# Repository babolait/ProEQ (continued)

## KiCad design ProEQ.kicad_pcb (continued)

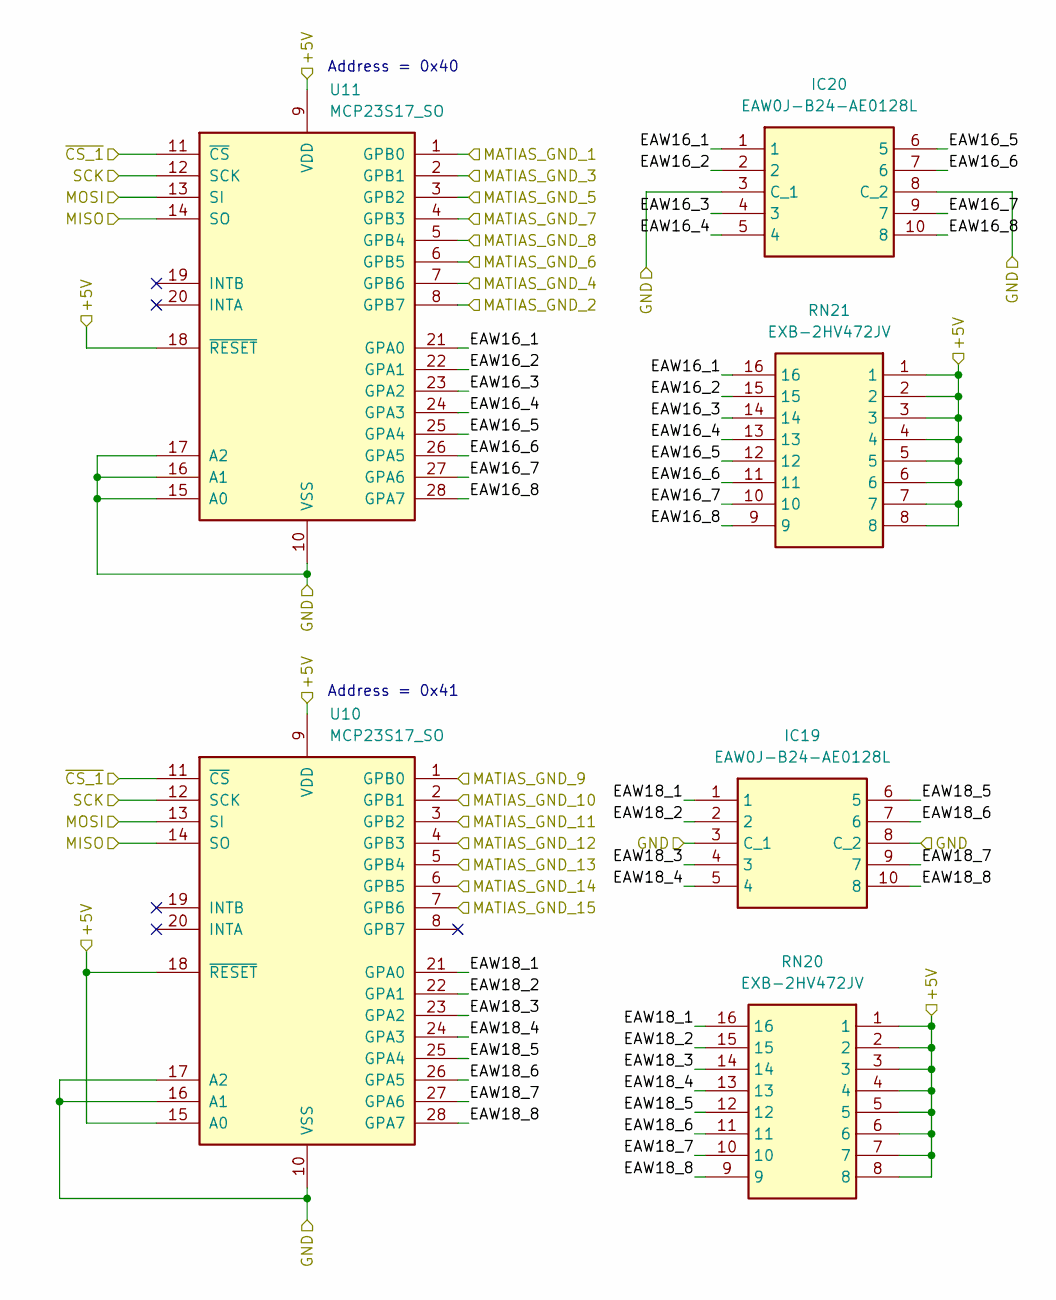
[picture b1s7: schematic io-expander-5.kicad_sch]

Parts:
IC19, IC20: EAW0J-B24-AE0128L; Manufacturer_Part_Number EAW0J-B24-AE0128L; Mouser Part Number 652-EAW0J-B24-AEL
RN20, RN21: EXB-2HV472JV; EXB2HV472JV; Manufacturer_Part_Number EXB-2HV472JV; Mouser Part Number 667-EXB-2HV472JV
U10, U11: MCP23S17_SO; SSOP-28_5.3x10.2mm_P0.65mm; Digikey REF MCP23S17-E/SS-ND

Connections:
+5V: RN20.1, RN20.2, RN20.3, RN20.4, RN20.5, RN20.6, RN20.7, RN20.8, RN21.1, RN21.2, RN21.3, RN21.4, RN21.5, RN21.6, RN21.7, RN21.8, U10.9 (VDD), U10.15 (A0), U10.18 (~RESET), U11.9 (VDD), U11.18 (~RESET); also elsewhere on the board
/IS31FL3743A1_2/MISO: U10.14 (SO), U11.14 (SO); also elsewhere on the board
/IS31FL3743A1_2/MOSI: U10.13 (SI), U11.13 (SI); also elsewhere on the board
/IS31FL3743A1_2/SCK: U10.12 (SCK), U11.12 (SCK); also elsewhere on the board
/MCP23017 + EAW_4/EAW16_1: IC20.1, RN21.16, U11.21 (GPA0)
/MCP23017 + EAW_4/EAW16_2: IC20.2, RN21.15, U11.22 (GPA1)
/MCP23017 + EAW_4/EAW16_3: IC20.4 (3), RN21.14, U11.23 (GPA2)
/MCP23017 + EAW_4/EAW16_4: IC20.5 (4), RN21.13, U11.24 (GPA3)
/MCP23017 + EAW_4/EAW16_5: IC20.6 (5), RN21.12, U11.25 (GPA4)
/MCP23017 + EAW_4/EAW16_6: IC20.7 (6), RN21.11, U11.26 (GPA5)
/MCP23017 + EAW_4/EAW16_7: IC20.9 (7), RN21.10, U11.27 (GPA6)
/MCP23017 + EAW_4/EAW16_8: IC20.10 (8), RN21.9, U11.28 (GPA7)
/MCP23017 + EAW_4/EAW18_1: IC19.1, RN20.16, U10.21 (GPA0)
/MCP23017 + EAW_4/EAW18_2: IC19.2, RN20.15, U10.22 (GPA1)
/MCP23017 + EAW_4/EAW18_3: IC19.4 (3), RN20.14, U10.23 (GPA2)
/MCP23017 + EAW_4/EAW18_4: IC19.5 (4), RN20.13, U10.24 (GPA3)
/MCP23017 + EAW_4/EAW18_5: IC19.6 (5), RN20.12, U10.25 (GPA4)
/MCP23017 + EAW_4/EAW18_6: IC19.7 (6), RN20.11, U10.26 (GPA5)
/MCP23017 + EAW_4/EAW18_7: IC19.9 (7), RN20.10, U10.27 (GPA6)
/MCP23017 + EAW_4/EAW18_8: IC19.10 (8), RN20.9, U10.28 (GPA7)
/MCP23017 + EAW_4/MATIAS_GND_1: U11.1 (GPB0); also elsewhere on the board
/MCP23017 + EAW_4/MATIAS_GND_2: U11.8 (GPB7); also elsewhere on the board
/MCP23017 + EAW_4/MATIAS_GND_3: U11.2 (GPB1); also elsewhere on the board
/MCP23017 + EAW_4/MATIAS_GND_4: U11.7 (GPB6); also elsewhere on the board
/MCP23017 + EAW_4/MATIAS_GND_5: U11.3 (GPB2); also elsewhere on the board
/MCP23017 + EAW_4/MATIAS_GND_6: U11.6 (GPB5); also elsewhere on the board
/MCP23017 + EAW_4/MATIAS_GND_7: U11.4 (GPB3); also elsewhere on the board
/MCP23017 + EAW_4/MATIAS_GND_8: U11.5 (GPB4); also elsewhere on the board
/MCP23017 + EAW_4/MATIAS_GND_9: U10.1 (GPB0); also elsewhere on the board
/MCP23017 + EAW_4/MATIAS_GND_10: U10.2 (GPB1); also elsewhere on the board
/MCP23017 + EAW_4/MATIAS_GND_11: U10.3 (GPB2); also elsewhere on the board
/MCP23017 + EAW_4/MATIAS_GND_12: U10.4 (GPB3); also elsewhere on the board
/MCP23017 + EAW_4/MATIAS_GND_13: U10.5 (GPB4); also elsewhere on the board
/MCP23017 + EAW_4/MATIAS_GND_14: U10.6 (GPB5); also elsewhere on the board
/MCP23017 + EAW_4/MATIAS_GND_15: U10.7 (GPB6); also elsewhere on the board
/MCP23017 + EAW_4/~CS_1: U10.11 (~CS), U11.11 (~CS); also elsewhere on the board
GND: IC19.3 (C_1), IC19.8 (C_2), IC20.3 (C_1), IC20.8 (C_2), U10.10 (VSS), U10.16 (A1), U10.17 (A2), U11.10 (VSS), U11.15 (A0), U11.16 (A1), U11.17 (A2); also elsewhere on the board

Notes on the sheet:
Address = 0x41
Address = 0x40

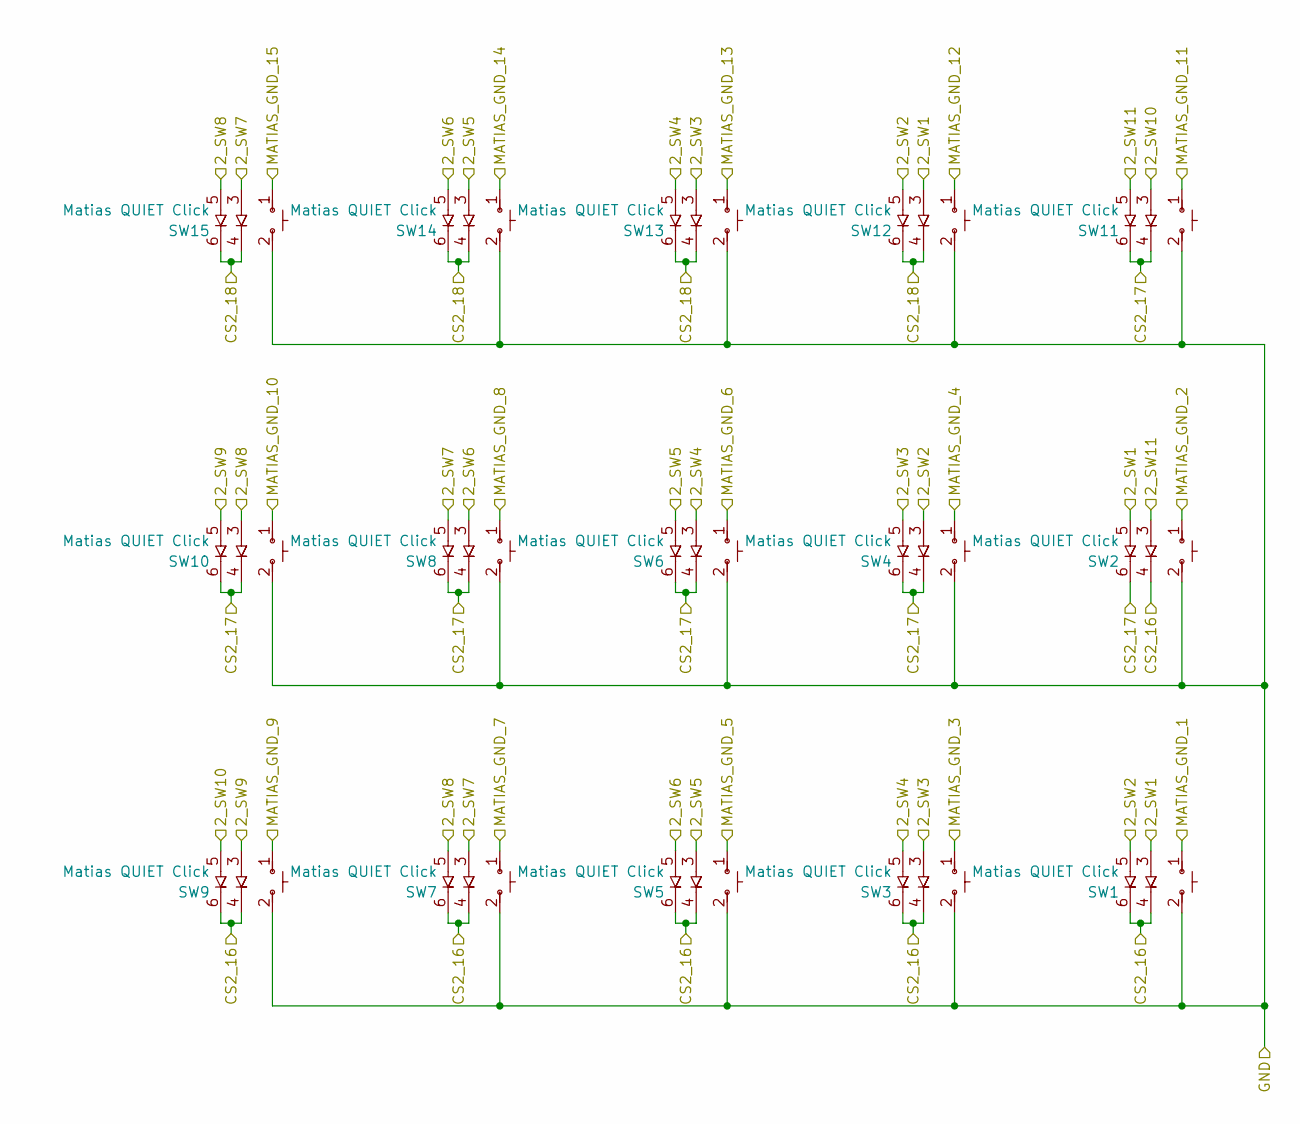
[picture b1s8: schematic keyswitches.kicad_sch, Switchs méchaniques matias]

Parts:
SW1, SW2, SW3, SW4, SW5, SW6, SW7, SW8, SW9, SW10, SW11, SW12, SW13, SW14, SW15: Matias QUIET Click; SW_Matias_QC_2LED

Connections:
/IS31FL3743A1_2/2_SW1: SW1.3, SW2.5, SW12.3; also elsewhere on the board
/IS31FL3743A1_2/2_SW2: SW1.5, SW4.3, SW12.5; also elsewhere on the board
/IS31FL3743A1_2/2_SW3: SW3.3, SW4.5, SW13.3; also elsewhere on the board
/IS31FL3743A1_2/2_SW4: SW3.5, SW6.3, SW13.5; also elsewhere on the board
/IS31FL3743A1_2/2_SW5: SW5.3, SW6.5, SW14.3; also elsewhere on the board
/IS31FL3743A1_2/2_SW6: SW5.5, SW8.3, SW14.5; also elsewhere on the board
/IS31FL3743A1_2/2_SW7: SW7.3, SW8.5, SW15.3; also elsewhere on the board
/IS31FL3743A1_2/2_SW8: SW7.5, SW10.3, SW15.5; also elsewhere on the board
/IS31FL3743A1_2/2_SW9: SW9.3, SW10.5; also elsewhere on the board
/IS31FL3743A1_2/2_SW10: SW9.5, SW11.3; also elsewhere on the board
/IS31FL3743A1_2/2_SW11: SW2.3, SW11.5; also elsewhere on the board
/IS31FL3743A1_2/CS2_16: SW1.4, SW1.6, SW2.4, SW3.4, SW3.6, SW5.4, SW5.6, SW7.4, SW7.6, SW9.4, SW9.6; also elsewhere on the board
/IS31FL3743A1_2/CS2_17: SW2.6, SW4.4, SW4.6, SW6.4, SW6.6, SW8.4, SW8.6, SW10.4, SW10.6, SW11.4, SW11.6; also elsewhere on the board
/IS31FL3743A1_2/CS2_18: SW12.4, SW12.6, SW13.4, SW13.6, SW14.4, SW14.6, SW15.4, SW15.6; also elsewhere on the board
/MCP23017 + EAW_4/MATIAS_GND_1: SW1.1; also elsewhere on the board
/MCP23017 + EAW_4/MATIAS_GND_2: SW2.1; also elsewhere on the board
/MCP23017 + EAW_4/MATIAS_GND_3: SW3.1; also elsewhere on the board
/MCP23017 + EAW_4/MATIAS_GND_4: SW4.1; also elsewhere on the board
/MCP23017 + EAW_4/MATIAS_GND_5: SW5.1; also elsewhere on the board
/MCP23017 + EAW_4/MATIAS_GND_6: SW6.1; also elsewhere on the board
/MCP23017 + EAW_4/MATIAS_GND_7: SW7.1; also elsewhere on the board
/MCP23017 + EAW_4/MATIAS_GND_8: SW8.1; also elsewhere on the board
/MCP23017 + EAW_4/MATIAS_GND_9: SW9.1; also elsewhere on the board
/MCP23017 + EAW_4/MATIAS_GND_10: SW10.1; also elsewhere on the board
/MCP23017 + EAW_4/MATIAS_GND_11: SW11.1; also elsewhere on the board
/MCP23017 + EAW_4/MATIAS_GND_12: SW12.1; also elsewhere on the board
/MCP23017 + EAW_4/MATIAS_GND_13: SW13.1; also elsewhere on the board
/MCP23017 + EAW_4/MATIAS_GND_14: SW14.1; also elsewhere on the board
/MCP23017 + EAW_4/MATIAS_GND_15: SW15.1; also elsewhere on the board
GND: SW1.2, SW2.2, SW3.2, SW4.2, SW5.2, SW6.2, SW7.2, SW8.2, SW9.2, SW10.2, SW11.2, SW12.2, SW13.2, SW14.2, SW15.2; also elsewhere on the board

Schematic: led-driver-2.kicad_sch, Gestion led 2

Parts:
C12, C14: 1uF; C_0603_1608Metric_Pad1.08x0.95mm_HandSolder; LCSC C15849
C13, C15, C16: 100nF; C_0603_1608Metric_Pad1.08x0.95mm_HandSolder; LCSC C14663
D201, D202, D203, D204, D212, D213, D214, D215, D223, D224, D225, D226, D234, D235, D236, D237, D245, D246, D247, D248, D256, D257, D258, D259, D267, D268, D269, D270, D278, D279, D280, D281, D289, D290, D291, D292, D300, D301, D302, D303, D311, D312, D313, D314, D322, D323, D324, D325, D333, D334, D335, D336, D344, D345, D346, D347, D355, D356, D357, D358, D366, D367, D368, D369, D377, D378, D379, D380, D388, D389, D390, D391: LED_inv; SMLZ24E2N3TT86_VLP; LCSC C20110232
R11: 10k; R_0603_1608Metric_Pad0.98x0.95mm_HandSolder; LCSC C25804
R12: 100k; R_0603_1608Metric_Pad0.98x0.95mm_HandSolder; LCSC C25803
R13, R14: 20; R_0603_1608Metric_Pad0.98x0.95mm_HandSolder; Digikey REF P20.00BYCT-ND
RN1, RN23: YC248-JR-0720RL; EXB2HV472JV; Manufacturer_Part_Number EXB-2HV472JV; Mouser Part Number 667-EXB-2HV472JV
U14: IS31FL3743B-QULS4-TR; IS31FL3743A; LCSC C2962218

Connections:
2_CS9: RN23.1, U14.31 (CS9)
2_CS10: RN23.2, U14.21 (CS10)
+5V: C12.1, C13.1, C14.1, C15.1, U14.5 (P_{VCC}), U14.22 (VCC); also elsewhere on the board
/IS31FL3743A1_2/2_SW1: D201.1 (A), D212.1 (A), D223.1 (A), D234.1 (A), D245.1 (A), D256.1 (A), D267.1 (A), D278.1 (A), D289.1 (A), D300.1 (A), D311.1 (A), D322.1 (A), D333.1 (A), D344.1 (A), D355.1 (A), D366.1 (A), D377.1 (A), D388.1 (A), U14.6 (SW1); also elsewhere on the board
/IS31FL3743A1_2/2_SW2: D202.1 (A), D213.1 (A), D224.1 (A), D235.1 (A), D246.1 (A), D257.1 (A), D268.1 (A), D279.1 (A), D290.1 (A), D301.1 (A), D312.1 (A), D323.1 (A), D334.1 (A), D345.1 (A), D356.1 (A), D367.1 (A), D378.1 (A), D389.1 (A), U14.4 (SW2); also elsewhere on the board
/IS31FL3743A1_2/2_SW3: D203.1 (A), D214.1 (A), D225.1 (A), D236.1 (A), D247.1 (A), D258.1 (A), D269.1 (A), D280.1 (A), D291.1 (A), D302.1 (A), D313.1 (A), D324.1 (A), D335.1 (A), D346.1 (A), D357.1 (A), D368.1 (A), D379.1 (A), D390.1 (A), U14.7 (SW3); also elsewhere on the board
/IS31FL3743A1_2/2_SW4: D204.1 (A), D215.1 (A), D226.1 (A), D237.1 (A), D248.1 (A), D259.1 (A), D270.1 (A), D281.1 (A), D292.1 (A), D303.1 (A), D314.1 (A), D325.1 (A), D336.1 (A), D347.1 (A), D358.1 (A), D369.1 (A), D380.1 (A), D391.1 (A), U14.3 (SW4); also elsewhere on the board
/IS31FL3743A1_2/2_SW5: U14.8 (SW5); also elsewhere on the board
/IS31FL3743A1_2/2_SW6: U14.2 (SW6); also elsewhere on the board
/IS31FL3743A1_2/2_SW7: U14.9 (SW7); also elsewhere on the board
/IS31FL3743A1_2/2_SW8: U14.1 (SW8); also elsewhere on the board
/IS31FL3743A1_2/2_SW9: U14.10 (SW9); also elsewhere on the board
/IS31FL3743A1_2/2_SW10: U14.40 (SW10); also elsewhere on the board
/IS31FL3743A1_2/2_SW11: U14.11 (SW11); also elsewhere on the board
/IS31FL3743A1_2/+3.3V: C16.1, R12.1, U14.26 (SDB); also elsewhere on the board
/IS31FL3743A1_2/CS2_16: D223.2 (K), D224.2 (K), D225.2 (K), D226.2 (K), RN23.9; also elsewhere on the board
/IS31FL3743A1_2/CS2_17: D212.2 (K), D213.2 (K), D214.2 (K), D215.2 (K), R14.2; also elsewhere on the board
/IS31FL3743A1_2/CS2_18: D201.2 (K), D202.2 (K), D203.2 (K), D204.2 (K), R13.2; also elsewhere on the board
/IS31FL3743A1_2/MISO: U14.24 (MISO); also elsewhere on the board
/IS31FL3743A1_2/MOSI: U14.28 (MOSI); also elsewhere on the board
/IS31FL3743A1_2/SCK: U14.27 (SCK); also elsewhere on the board
/IS31FL3743A1_2/~CS_2: U14.25 (~CS); also elsewhere on the board
CS2_1: D388.2 (K), D389.2 (K), D390.2 (K), D391.2 (K), RN1.8
CS2_2: D377.2 (K), D378.2 (K), D379.2 (K), D380.2 (K), RN1.7
CS2_3: D366.2 (K), D367.2 (K), D368.2 (K), D369.2 (K), RN1.6
CS2_4: D355.2 (K), D356.2 (K), D357.2 (K), D358.2 (K), RN1.5
CS2_5: D344.2 (K), D345.2 (K), D346.2 (K), D347.2 (K), RN1.4
CS2_6: D333.2 (K), D334.2 (K), D335.2 (K), D336.2 (K), RN1.3
CS2_7: D322.2 (K), D323.2 (K), D324.2 (K), D325.2 (K), RN1.2
CS2_8: D311.2 (K), D312.2 (K), D313.2 (K), D314.2 (K), RN1.1
CS2_9: D300.2 (K), D301.2 (K), D302.2 (K), D303.2 (K), RN23.16
CS2_10: D289.2 (K), D290.2 (K), D291.2 (K), D292.2 (K), RN23.15
CS2_11: D278.2 (K), D279.2 (K), D280.2 (K), D281.2 (K), RN23.14
CS2_12: D267.2 (K), D268.2 (K), D269.2 (K), D270.2 (K), RN23.13
CS2_13: D256.2 (K), D257.2 (K), D258.2 (K), D259.2 (K), RN23.12
CS2_14: D245.2 (K), D246.2 (K), D247.2 (K), D248.2 (K), RN23.11
CS2_15: D234.2 (K), D235.2 (K), D236.2 (K), D237.2 (K), RN23.10
GND: C12.2, C13.2, C14.2, C15.2, C16.2, R11.2, R12.2, U14.16 (P_{GND}), U14.23 (GND), U14.41 (P_{GND}); also elsewhere on the board
unnamed: RN1.9, U14.39 (CS1)
unnamed: RN1.10, U14.38 (CS2)
unnamed: RN1.11, U14.37 (CS3)
unnamed: RN1.12, U14.36 (CS4)
unnamed: RN1.13, U14.35 (CS5)
unnamed: RN1.14, U14.34 (CS6)
unnamed: RN1.15, U14.33 (CS7)
unnamed: RN1.16, U14.32 (CS8)
unnamed: RN23.3, U14.20 (CS11)
unnamed: RN23.4, U14.19 (CS12)
unnamed: RN23.5, U14.18 (CS13)
unnamed: RN23.6, U14.17 (CS14)
unnamed: RN23.7, U14.15 (CS15)
unnamed: RN23.8, U14.14 (CS16)
unnamed: R14.1, U14.13 (CS17)
unnamed: R13.1, U14.12 (CS18)
unnamed: R11.1, U14.29 (I_{set})

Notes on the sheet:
address = 0bX101000X
The 20R and 50R between LED and IC is only for thermal reduction, for mono red LED, if PV CC =V CC =3.3V, don't need these resistors
OUTs for SW LEDS

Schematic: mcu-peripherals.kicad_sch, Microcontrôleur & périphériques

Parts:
A1: Arduino_UNO_R3
J2: Conn_01x07; PinHeader_1x07_P2.54mm_Vertical
J4, J6: Conn_01x11; PinHeader_1x11_P2.54mm_Vertical
J5, J16: Conn_01x01; PinHeader_1x01_P2.54mm_Vertical
R4, R5: 4k7; R_0603_1608Metric_Pad0.98x0.95mm_HandSolder; Digikey REF RMCF0603FT4K70CT-ND
R15, R16, R17, R18, R19, R20, R21, R22, R23, R24, R25, R26, R27, R28, R29, R30, R31, R32, R33, R34: 10k; R_0603_1608Metric_Pad0.98x0.95mm_HandSolder; Digikey REF RMCF0603JT10K0CT-ND
TP1, TP2, TP5, TP6, TP7, TP8, TP9, TP11, TP12, TP13: TestPoint; PinHeader_1x01_P2.54mm_Vertical

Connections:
+5V: J4.1, J6.1, R4.1, R5.1, R16.1, R25.1; also elsewhere on the board
/Alimentation/+5V USB: A1.5 (+5V); also elsewhere on the board
/IS31FL3743A1_2/+3.3V: A1.4 (3V3); also elsewhere on the board
/IS31FL3743A1_2/MISO: A1.27 (D12), TP8.1; also elsewhere on the board
/IS31FL3743A1_2/MOSI: A1.26 (D11), TP7.1; also elsewhere on the board
/IS31FL3743A1_2/SCK: A1.28 (D13), TP9.1; also elsewhere on the board
/IS31FL3743A1_2/~CS_2: A1.12 (A3), TP13.1; also elsewhere on the board
/MCP23017 + EAW/~CS_0: A1.17 (D2), TP11.1; also elsewhere on the board
/MCP23017 + EAW_4/~CS_1: A1.18 (D3), TP12.1; also elsewhere on the board
GND: A1.6 (GND), A1.7 (GND), A1.29 (GND), J4.11, J6.11, R24.2, R34.2; also elsewhere on the board
unnamed: A1.9 (A0), J5.1
unnamed: A1.10 (A1), J16.1
unnamed: A1.15 (D0/RX), TP1.1
unnamed: A1.16 (D1/TX), TP2.1
unnamed: A1.19 (D4), J2.1
unnamed: A1.20 (D5), J2.2
unnamed: A1.21 (D6), J2.3
unnamed: A1.22 (D7), J2.4
unnamed: A1.23 (D8), J2.5
unnamed: A1.24 (D9), J2.6
unnamed: A1.25 (D10), J2.7
unnamed: A1.14 (SCL/A5), R5.2, TP6.1
unnamed: A1.13 (SDA/A4), R4.2, TP5.1
unnamed: J4.2, R15.1, R16.2
unnamed: J4.3, R15.2, R17.1
unnamed: J4.4, R17.2, R18.1
unnamed: J4.5, R18.2, R19.1
unnamed: J4.6, R19.2, R20.1
unnamed: J4.7, R20.2, R21.1
unnamed: J4.8, R21.2, R22.1
unnamed: J4.9, R22.2, R23.1
unnamed: J4.10, R23.2, R24.1
unnamed: J6.2, R25.2, R26.1
unnamed: J6.3, R26.2, R27.1
unnamed: J6.4, R27.2, R28.1
unnamed: J6.5, R28.2, R29.1
unnamed: J6.6, R29.2, R30.1
unnamed: J6.7, R30.2, R31.1
unnamed: J6.8, R31.2, R32.1
unnamed: J6.9, R32.2, R33.1
unnamed: J6.10, R33.2, R34.1

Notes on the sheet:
Resistor ladder

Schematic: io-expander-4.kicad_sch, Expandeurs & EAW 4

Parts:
IC14, IC15, IC16, IC17: EAW0J-B24-AE0128L; Manufacturer_Part_Number EAW0J-B24-AE0128L; Mouser Part Number 652-EAW0J-B24-AEL
RN15, RN16, RN17, RN18: EXB-2HV472JV; EXB2HV472JV; Manufacturer_Part_Number EXB-2HV472JV; Mouser Part Number 667-EXB-2HV472JV
U8, U9: MCP23S17_SO; SSOP-28_5.3x10.2mm_P0.65mm; Digikey REF MCP23S17-E/SS-ND

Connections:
+5V: RN15.1, RN15.2, RN15.3, RN15.4, RN15.5, RN15.6, RN15.7, RN15.8, RN16.1, RN16.2, RN16.3, RN16.4, RN16.5, RN16.6, RN16.7, RN16.8, RN17.1, RN17.2, RN17.3, RN17.4, RN17.5, RN17.6, RN17.7, RN17.8, RN18.1, RN18.2, RN18.3, RN18.4, RN18.5, RN18.6, RN18.7, RN18.8, U8.9 (VDD), U8.16 (A1), U8.17 (A2), U8.18 (~RESET), U9.9 (VDD), U9.15 (A0), U9.16 (A1), U9.17 (A2), U9.18 (~RESET); also elsewhere on the board
/IS31FL3743A1_2/MISO: U8.14 (SO), U9.14 (SO); also elsewhere on the board
/IS31FL3743A1_2/MOSI: U8.13 (SI), U9.13 (SI); also elsewhere on the board
/IS31FL3743A1_2/SCK: U8.12 (SCK), U9.12 (SCK); also elsewhere on the board
/MCP23017 + EAW/~CS_0: U8.11 (~CS), U9.11 (~CS); also elsewhere on the board
/MCP23017 + EAW_3/EAW12_1: IC16.1, RN17.16, U8.21 (GPA0)
/MCP23017 + EAW_3/EAW12_2: IC16.2, RN17.15, U8.22 (GPA1)
/MCP23017 + EAW_3/EAW12_3: IC16.4 (3), RN17.14, U8.23 (GPA2)
/MCP23017 + EAW_3/EAW12_4: IC16.5 (4), RN17.13, U8.24 (GPA3)
/MCP23017 + EAW_3/EAW12_5: IC16.6 (5), RN17.12, U8.25 (GPA4)
/MCP23017 + EAW_3/EAW12_6: IC16.7 (6), RN17.11, U8.26 (GPA5)
/MCP23017 + EAW_3/EAW12_7: IC16.9 (7), RN17.10, U8.27 (GPA6)
/MCP23017 + EAW_3/EAW12_8: IC16.10 (8), RN17.9, U8.28 (GPA7)
/MCP23017 + EAW_3/EAW13_1: IC14.1, RN15.16, U8.1 (GPB0)
/MCP23017 + EAW_3/EAW13_2: IC14.2, RN15.15, U8.2 (GPB1)
/MCP23017 + EAW_3/EAW13_3: IC14.4 (3), RN15.14, U8.3 (GPB2)
/MCP23017 + EAW_3/EAW13_4: IC14.5 (4), RN15.13, U8.4 (GPB3)
/MCP23017 + EAW_3/EAW13_5: IC14.6 (5), RN15.12, U8.5 (GPB4)
/MCP23017 + EAW_3/EAW13_6: IC14.7 (6), RN15.11, U8.6 (GPB5)
/MCP23017 + EAW_3/EAW13_7: IC14.9 (7), RN15.10, U8.7 (GPB6)
/MCP23017 + EAW_3/EAW13_8: IC14.10 (8), RN15.9, U8.8 (GPB7)
/MCP23017 + EAW_3/EAW14_1: IC17.1, RN18.16, U9.21 (GPA0)
/MCP23017 + EAW_3/EAW14_2: IC17.2, RN18.15, U9.22 (GPA1)
/MCP23017 + EAW_3/EAW14_3: IC17.4 (3), RN18.14, U9.23 (GPA2)
/MCP23017 + EAW_3/EAW14_4: IC17.5 (4), RN18.13, U9.24 (GPA3)
/MCP23017 + EAW_3/EAW14_5: IC17.6 (5), RN18.12, U9.25 (GPA4)
/MCP23017 + EAW_3/EAW14_6: IC17.7 (6), RN18.11, U9.26 (GPA5)
/MCP23017 + EAW_3/EAW14_7: IC17.9 (7), RN18.10, U9.27 (GPA6)
/MCP23017 + EAW_3/EAW14_8: IC17.10 (8), RN18.9, U9.28 (GPA7)
/MCP23017 + EAW_3/EAW15_1: IC15.1, RN16.16, U9.1 (GPB0)
/MCP23017 + EAW_3/EAW15_2: IC15.2, RN16.15, U9.2 (GPB1)
/MCP23017 + EAW_3/EAW15_3: IC15.4 (3), RN16.14, U9.3 (GPB2)
/MCP23017 + EAW_3/EAW15_4: IC15.5 (4), RN16.13, U9.4 (GPB3)
/MCP23017 + EAW_3/EAW15_5: IC15.6 (5), RN16.12, U9.5 (GPB4)
/MCP23017 + EAW_3/EAW15_6: IC15.7 (6), RN16.11, U9.6 (GPB5)
/MCP23017 + EAW_3/EAW15_7: IC15.9 (7), RN16.10, U9.7 (GPB6)
/MCP23017 + EAW_3/EAW15_8: IC15.10 (8), RN16.9, U9.8 (GPB7)
GND: IC14.3 (C_1), IC14.8 (C_2), IC15.3 (C_1), IC15.8 (C_2), IC16.3 (C_1), IC16.8 (C_2), IC17.3 (C_1), IC17.8 (C_2), U8.10 (VSS), U8.15 (A0), U9.10 (VSS); also elsewhere on the board

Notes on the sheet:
Address = 0x47
Address = 0x46

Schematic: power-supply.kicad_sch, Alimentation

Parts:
C1: 100nF; C_0603_1608Metric_Pad1.08x0.95mm_HandSolder; LCSC C14663
C2: 10pF; C_0603_1608Metric_Pad1.08x0.95mm_HandSolder; LCSC C1634
C3, C4: 22uF; C_0805_2012Metric; Digikey REF 22uF,1276-2910-1-ND
C5: 100uF; CP_Radial_D5.0mm_P2.00mm; Digikey REF 1189-25YXS100MEFC5X11-ND
C6: 10uF; C_0603_1608Metric_Pad1.08x0.95mm_HandSolder; Digikey REF 445-C1608X5R1E106M080DCCT-ND
C17, C18: 1uF; C_0805_2012Metric; LCSC C28323
D1: PMEG4030ER; Nexperia_CFP3_SOD-123W; Digikey REF 5272-PMEG4030ERCT-ND
D2: vert; D_0805_2012Metric_Pad1.15x1.40mm_HandSolder; Digikey REF 754-1127-1-ND
J1: Power IN (<9V); PinHeader_1x02_P2.54mm_Vertical
L1: 3,3uH; L_Changjiang_FNR6040S; Digikey REF 732-5545-1-ND
R1: 52,3k; R_0603_1608Metric_Pad0.98x0.95mm_HandSolder; Digikey REF CR0603-FX-5232ELFCT-ND
R2: 1k; R_0603_1608Metric_Pad0.98x0.95mm_HandSolder; Digikey REF 311-1.00KHRCT-ND
R3, R35: 10k; R_0603_1608Metric_Pad0.98x0.95mm_HandSolder; Digikey REF RMCF0603JT10K0CT-ND
TP4, TP10: TestPoint; PinHeader_1x01_P2.54mm_Vertical
U1: AP62301WU; TSOT-23-6_HandSoldering; Digikey REF 31-AP62301WU-7CT-ND
U12: LM66200DRLR; SOT-583-8_HandSolder; LCSC C3235556

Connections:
+5V: TP10.1, U12.2 (V_{out}), U12.7 (V_{out}); also elsewhere on the board
/Alimentation/+5V USB: C18.1, U12.6 (V_{in2}); also elsewhere on the board
/Alimentation/SW FOR COPPER AREA: C1.1, L1.1, U1.2 (SW)
/Alimentation/VIN FOR COPPER: C5.1, C6.1, D1.1 (K), U1.3 (IN)
/Alimentation/Zone Vin 1: C2.1, C3.1, C4.1, C17.1, L1.2, R1.1, R2.1, R35.1, U12.3 (V_{in1})
GND: C3.2, C4.2, C5.2, C6.2, C17.2, C18.2, D2.1 (K), J1.1, R3.2, TP4.1, U1.1 (GND), U12.1 (GND), U12.5 (GND); also elsewhere on the board
unnamed: D1.2 (A), J1.2
unnamed: D2.2 (A), R2.2
unnamed: C1.2, U1.6 (BST)
unnamed: C2.2, R1.2, R3.1, U1.4 (FB)
unnamed: R35.2, U12.8 (ST)

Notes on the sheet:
1.5A peak
Decoupling for LM66 inputs
25mA par MCP23s17 9 x 25 = 225 mA 40mA par matias led 15 x 40 = 600 mA 1mA par led 271 x 1 --> 300 mA 190mA pour VFD 1 x 190 = 190 mA 30 mA pour Arduino 1 x 30 = 30 mA = 1,345 A -->

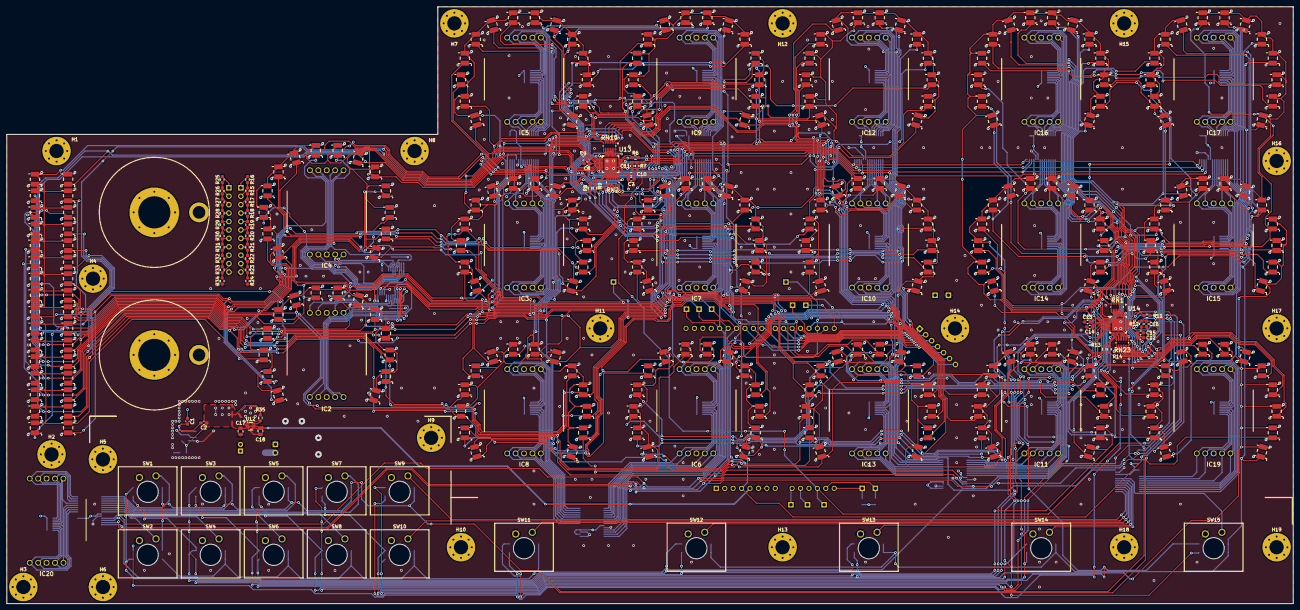
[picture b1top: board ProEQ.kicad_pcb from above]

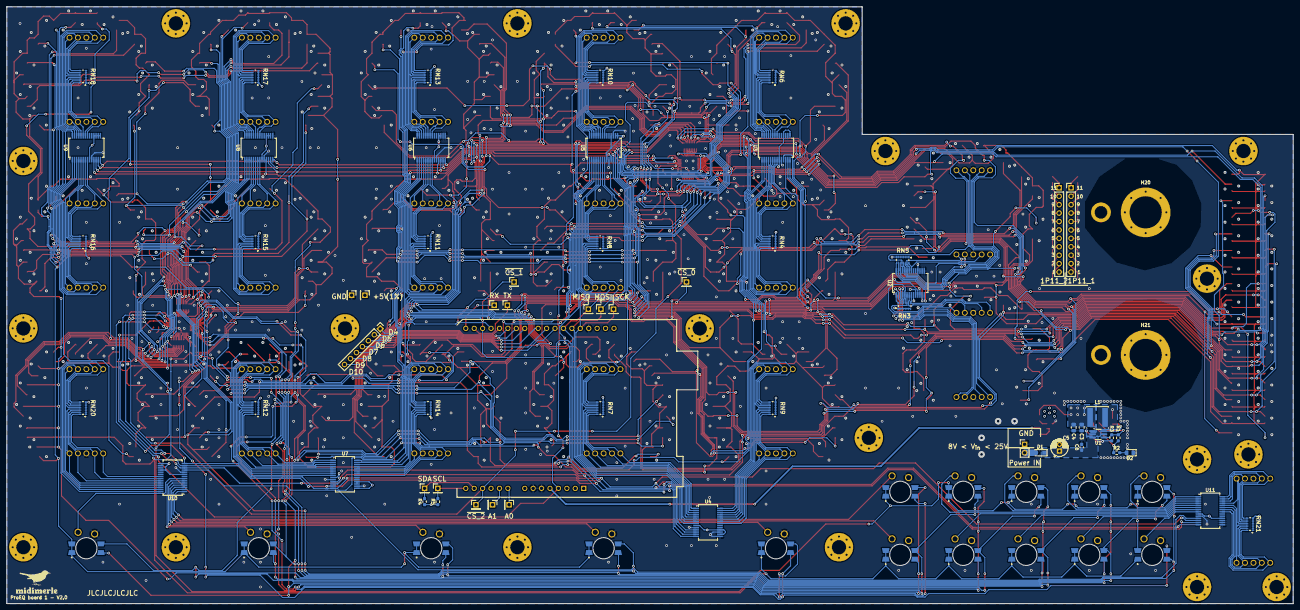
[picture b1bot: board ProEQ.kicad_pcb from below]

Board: 4 copper layers, 388.0 x 180.0 mm, 435 parts (63 on the bottom side), 304 nets.

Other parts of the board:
FID1: Fiducial; midimerle_logo

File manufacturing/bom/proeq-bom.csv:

Id,Designator,Footprint,Quantity,Designation,Supplier and ref
1,"D91,D96,D224,D160,D156,D259,D99,D38,D183,D143,D23,D116,D281,D124,D130,D155,D15,D225,D82,D24,D301,D55,D77,D193,D292,D10,D92,D270,D290,D366,D54,D192,D136,D27,D347,D68,D335,D133,D153,D102,D111,D36,D336,D53,D70,D109,D86,D61,D11,D345,D369,D158,D267,D83,D13,D177,D9,D245,D94,D379,D72,D151,D247,D118,D181,D166,D76,D95,D174,D106,D122,D291,D81,D129,D197,D182,D186,D171,D324,D58,D110,D78,D356,D149,D333,D170,D185,D191,D390,D300,D164,D148,D289,D314,D367,D131,D16,D355,D202,D269,D34,D45,D223,D120,D97,D258,D246,D180,D44,D163,D146,D165,D4,D37,D280,D113,D25,D90,D43,D69,D187,D66,D388,D257,D346,D79,D127,D57,D162,D107,D179,D167,D157,D65,D134,D5,D126,D85,D168,D64,D358,D237,D132,D80,D20,D196,D215,D380,D204,D52,D368,D26,D98,D137,D123,D18,D150,D29,D101,D22,D117,D142,D41,D311,D175,D60,D173,D62,D121,D105,D89,D378,D313,D84,D235,D3,D47,D154,D322,D138,D279,D88,D391,D188,D21,D6,D14,D140,D214,D147,D114,D31,D389,D161,D139,D112,D312,D56,D213,D12,D323,D203,D42,D28,D145,D152,D103,D48,D115,D59,D51,D234,D248,D268,D377,D75,D67,D35,D30,D172,D194,D108,D87,D190,D49,D189,D199,D201,D226,D135,D176,D344,D8,D357,D32,D93,D184,D212,D256,D325,D159,D74,D198,D17,D19,D141,D169,D236,D303,D178,D200,D46,D278,D73,D33,D71,D104,D195,D119,D302,D50,D39,D128,D100,D144,D125,D63,D40,D7,D334",SMLZ24E2N3TT86 + VLP,270,LED_inv,846-SMLZ24E2N3TT86CT-ND
2,"C13,C8,C15,C11,C10,C16",C_0603_1608Metric_Pad1.08x0.95mm_HandSolder,6,"0,1uF",1276-1935-1-ND
3,"IC15,IC5,IC11,IC12,IC6,IC9,IC4,IC19,IC3,IC13,IC8,IC10,IC14,IC2,IC16,IC7,IC17,IC20",EAW0J-B24-AE0128L,18,EAW0J-B24-AE0128L,EAW0J-B24-AE0128L-ND
4,"H14,H19,H1,H12,H8,H18,H11,H2,H17,H6,H3,H16,H5,H9,H7,H10,H4,H13,H15",MountingHole_4.5mm_Pad_Via,19,MountingHole_Pad,
5,"SW8,SW4,SW13,SW11,SW12,SW9,SW6,SW1,SW5,SW2,SW14,SW3,SW15,SW7,SW10",SW_Matias_QC,15,Matias QUIET Click,
6,"RN23,RN19,RN1,RN2",EXB2HV472JV,4,YC248-JR-0720RL,13-YC248-JR-0720RLCT-ND
7,C1,C_1206_3216Metric,1,100nF,1276-1017-1-ND
8,"R13,R9,R8,R14",R_0603_1608Metric_Pad0.98x0.95mm_HandSolder,4,20,P20.00BYCT-ND
9,"C9,C14,C7,C12",C_0603_1608Metric_Pad1.08x0.95mm_HandSolder,4,1uF,1276-1102-1-ND
10,"R7,R12,A13,A2,A7,A23,R10,A16,A4,A15,A14,A19,A9,A12,A10,A18,A21,A22,A24,A26,A8,A17,A11,A27,A30,A5,A25,A6,A29,A20,A3,A31",R_0603_1608Metric_Pad0.98x0.95mm_HandSolder,32,100k,311-100KHRCT-ND
11,C2,C_1206_3216Metric,1,10pF,738-CML1206C0G100JT50VCT-ND
12,"IC21,IC1",IS31FL3743A,2,IS31FL3743A-QULS4-TR,2521-IS31FL3743A-QULS4-TRCT-ND
13,"R6,R11",R_0603_1608Metric_Pad0.98x0.95mm_HandSolder,2,10k,RMCF0603JT10K0CT-ND
14,"U2,U8,U4,U6,U10,U3,U5,U7,U11,U9",SSOP-28_5.3x10.2mm_P0.65mm,10,MCP23S17_SO,MCP23S17T-E/SSCT-ND
15,FID1,midimerleKicad symbol,1,Fiducial,
16,R2,R_0805_2012Metric_Pad1.20x1.40mm_HandSolder,1,1k,RR12P1.0KDCT-ND
17,A1,Arduino_UNO_R3_modified,1,Arduino_UNO_R3_modified,
18,"C3,C4",C_1206_3216Metric,2,22uF,276-2728-1-ND
19,L1,L_Changjiang_FNR6040S,1,"3,3uH",732-5545-1-ND
20,"RN18,RN15,RN6,RN20,RN9,RN21,RN3,RN17,RN11,RN13,RN5,RN8,RN10,RN7,RN14,RN16,RN4,RN12",EXB2HV472JV,18,EXB-2HV472JV,Y1472CT-ND
21,"TP9,TP8,TP1,TP5,TP2,TP6,TP3,TP4,TP7",PinHeader_1x01_P2.54mm_Vertical,9,TestPoint,
22,R3,R_0805_2012Metric_Pad1.20x1.40mm_HandSolder,1,10k,P10KACT-ND
23,D2,D_0805_2012Metric_Pad1.15x1.40mm_HandSolder,1,vert,754-1127-1-ND
24,J1,PinHeader_1x02_P2.54mm_Vertical,1,Power IN (<9V),
25,A28,R_0603_1608Metric_Pad0.98x0.95mm_HandSolder,1,0,RMCF0603ZT0R00CT-ND
26,U1,TSOT-23-6_HandSoldering,1,AP62301WU,31-AP62301WU-7CT-ND
27,C6,C_1206_3216Metric,1,10uF,1276-2876-1-ND
28,C5,CP_Radial_D5.0mm_P2.00mm,1,100uF,1189-25YXS100MEFC5X11-ND
29,"R4,R5",R_0805_2012Metric_Pad1.20x1.40mm_HandSolder,2,4k7,541-4131-1-ND
30,D1,Nexperia_CFP3_SOD-123W,1,PMEG4030ER,5272-PMEG4030ERCT-ND
31,R1,R_0805_2012Metric_Pad1.20x1.40mm_HandSolder,1,"52,3k",
32,Cavalier,ADDED,1,2.54mm,
33,1P11,ADDED,2,,CT2122-ND
34,Knob head ACE large,ADDED,17,1913BC ?,
35,Knob head ACE small,ADDED,1,,

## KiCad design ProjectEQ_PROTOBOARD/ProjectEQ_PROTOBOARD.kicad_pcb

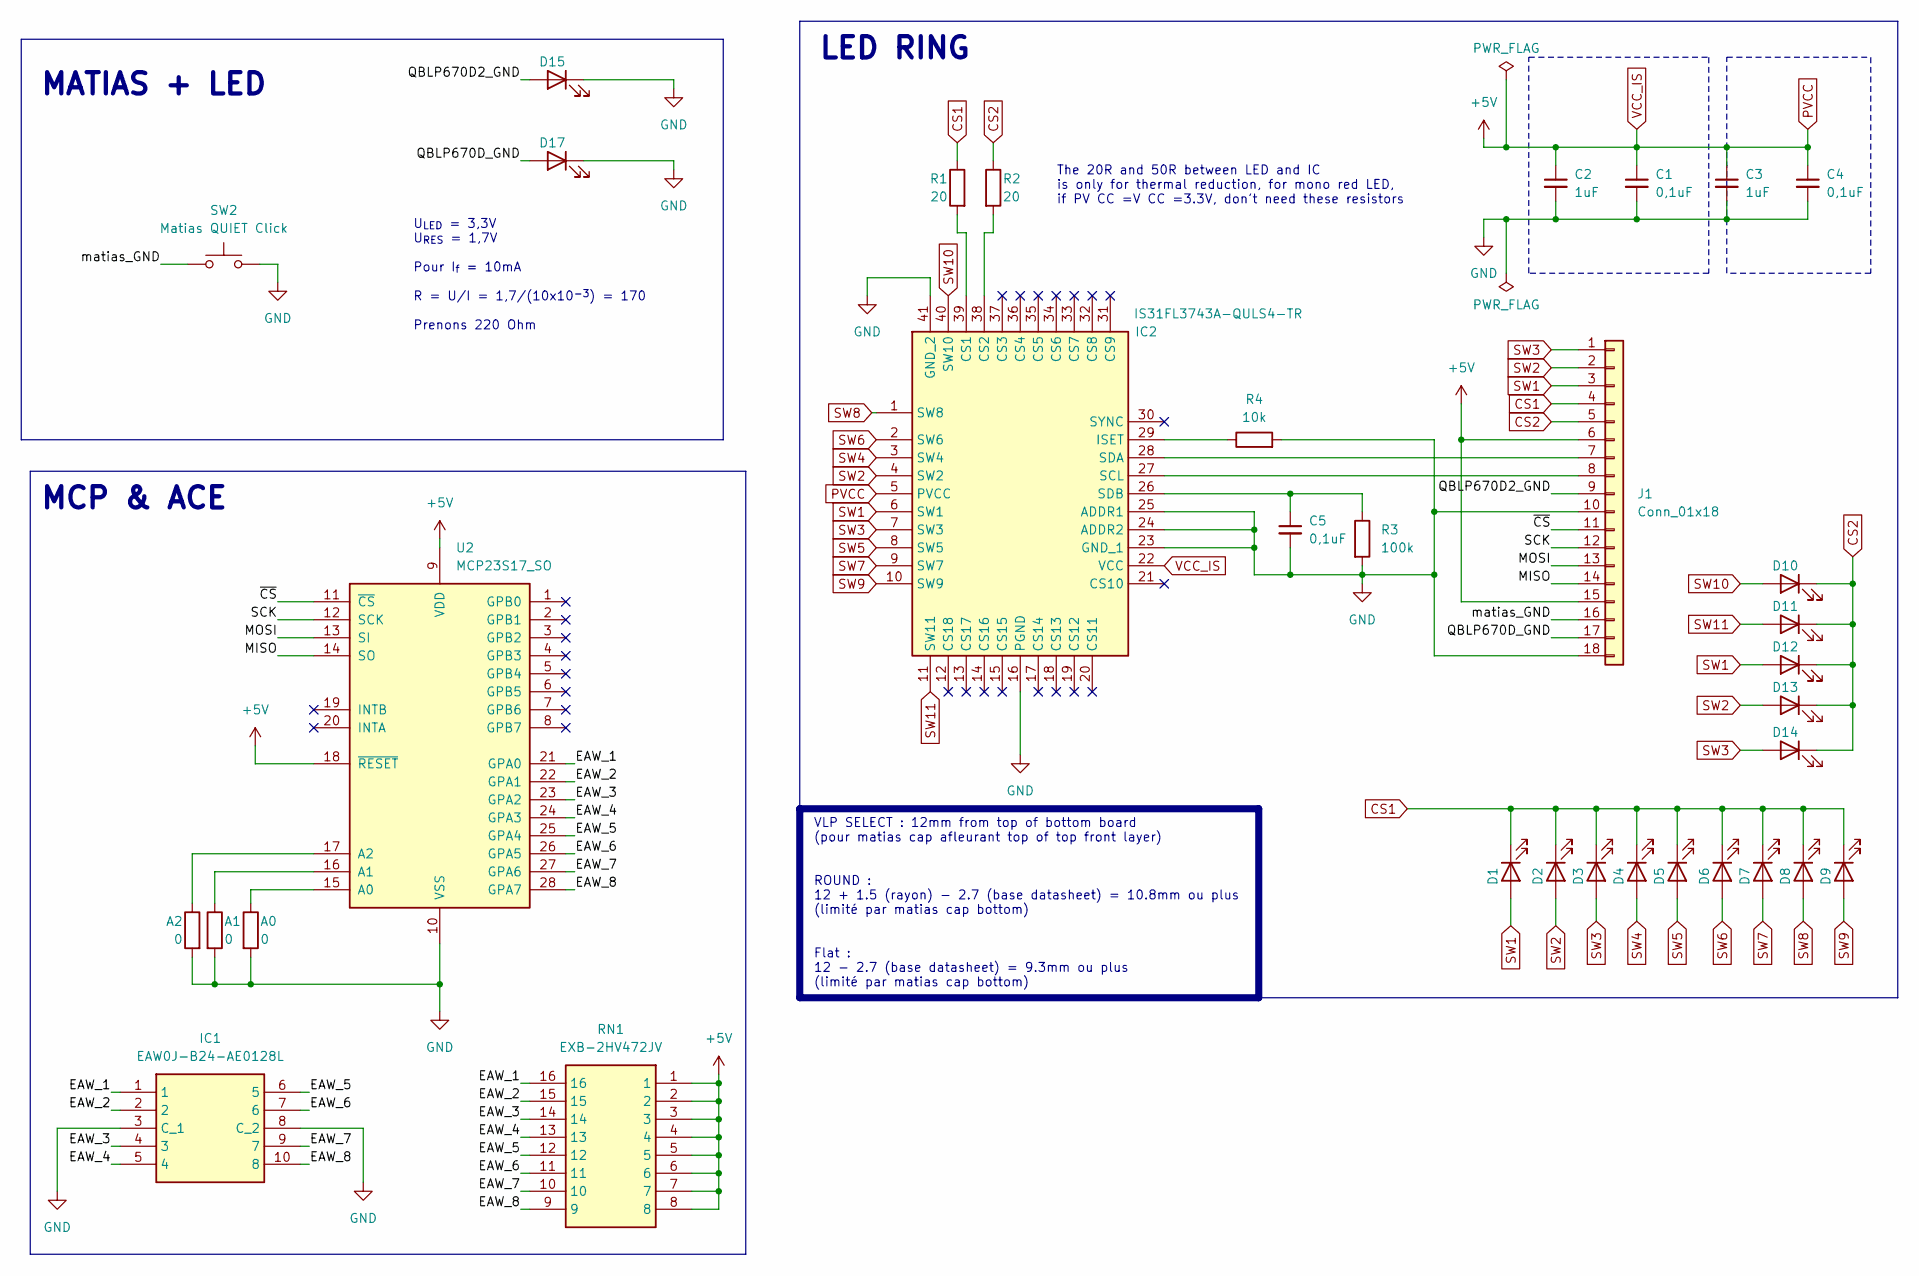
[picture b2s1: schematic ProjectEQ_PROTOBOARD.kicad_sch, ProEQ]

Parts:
A0, A1, A2: 0; R_0603_1608Metric_Pad0.98x0.95mm_HandSolder
C1, C4, C5: 0,1uF; C_0603_1608Metric_Pad1.08x0.95mm_HandSolder
C2, C3: 1uF; C_0603_1608Metric_Pad1.08x0.95mm_HandSolder
D1, D2, D3, D4, D5, D6, D7, D8, D9, D10, D11, D12, D13, D14: LED_inv; SMLZ24E2N3TT86
D15, D17: LED_inv; SMLZ24E2N3TT86_SPEMAT
IC1: EAW0J-B24-AE0128L; Manufacturer_Part_Number EAW0J-B24-AE0128L; Mouser Part Number 652-EAW0J-B24-AEL
IC2: IS31FL3743A-QULS4-TR; IS31FL3743A; Manufacturer_Part_Number IS31FL3743A-QULS4-TR; Mouser Part Number 870-I31FL3743AQULS4T
J1: Conn_01x18; PinHeader_1x18_P2.54mm_Vertical
R1, R2: 20; R_0603_1608Metric_Pad0.98x0.95mm_HandSolder
R3: 100k; R_0603_1608Metric_Pad0.98x0.95mm_HandSolder
R4: 10k; R_0603_1608Metric_Pad0.98x0.95mm_HandSolder
RN1: EXB-2HV472JV; EXB2HV472JV; Manufacturer_Part_Number EXB-2HV472JV; Mouser Part Number 667-EXB-2HV472JV
SW2: Matias QUIET Click; SW_Matias_QC
U2: MCP23S17_SO; SSOP-28_5.3x10.2mm_P0.65mm

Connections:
/EAW_1: IC1.1, RN1.16, U2.21 (GPA0)
/EAW_2: IC1.2, RN1.15, U2.22 (GPA1)
/EAW_3: IC1.4 (3), RN1.14, U2.23 (GPA2)
/EAW_4: IC1.5 (4), RN1.13, U2.24 (GPA3)
/EAW_5: IC1.6 (5), RN1.12, U2.25 (GPA4)
/EAW_6: IC1.7 (6), RN1.11, U2.26 (GPA5)
/EAW_7: IC1.9 (7), RN1.10, U2.27 (GPA6)
/EAW_8: IC1.10 (8), RN1.9, U2.28 (GPA7)
/MISO: J1.14, U2.14 (SO)
/MOSI: J1.13, U2.13 (SI)
/QBLP670D2_GND: D15.1 (A), J1.9
/QBLP670D_GND: D17.1 (A), J1.17
/SCK: J1.12, U2.12 (SCK)
/matias_GND: J1.16, SW2.1
/~CS: J1.11, U2.11 (~CS)
CS1: D1.2 (K), D2.2 (K), D3.2 (K), D4.2 (K), D5.2 (K), D6.2 (K), D7.2 (K), D8.2 (K), D9.2 (K), J1.4, R1.1
CS2: D10.2 (K), D11.2 (K), D12.2 (K), D13.2 (K), D14.2 (K), J1.5, R2.1
GND: A0.2, A1.2, A2.2, C1.2, C2.2, C3.2, C4.2, C5.2, D15.2 (K), D17.2 (K), IC1.3 (C_1), IC1.8 (C_2), IC2.16 (PGND), IC2.23 (GND_1), IC2.24 (ADDR2), IC2.25 (ADDR1), IC2.41 (GND_2), J1.10, J1.18, R3.2, R4.2, SW2.2, U2.10 (VSS)
unnamed: IC2.39 (CS1), R1.2
unnamed: IC2.38 (CS2), R2.2
unnamed: IC2.29 (ISET), R4.1
unnamed: IC2.27 (SCL), J1.8
unnamed: IC2.28 (SDA), J1.7
unnamed: C5.1, IC2.26 (SDB), R3.1
unnamed: A0.1, U2.15 (A0)
unnamed: A1.1, U2.16 (A1)
unnamed: A2.1, U2.17 (A2)
PVCC: C1.1, C2.1, C3.1, C4.1, IC2.5 (PVCC), IC2.22 (VCC), J1.6, J1.15, RN1.1, RN1.2, RN1.3, RN1.4, RN1.5, RN1.6, RN1.7, RN1.8, U2.9 (VDD), U2.18 (~RESET)
SW1: D1.1 (A), D12.1 (A), IC2.6 (SW1), J1.3
SW2: D2.1 (A), D13.1 (A), IC2.4 (SW2), J1.2
SW3: D3.1 (A), D14.1 (A), IC2.7 (SW3), J1.1
SW4: D4.1 (A), IC2.3 (SW4)
SW5: D5.1 (A), IC2.8 (SW5)
SW6: D6.1 (A), IC2.2 (SW6)
SW7: D7.1 (A), IC2.9 (SW7)
SW8: D8.1 (A), IC2.1 (SW8)
SW9: D9.1 (A), IC2.10 (SW9)
SW10: D10.1 (A), IC2.40 (SW10)
SW11: D11.1 (A), IC2.11 (SW11)

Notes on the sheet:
MCP & ACE
U_{LED} = 3,3V U_{RES} = 1,7V Pour I_{f} = 10mA R = U/I = 1,7/(10x10^{-3}) = 170 Prenons 220 Ohm
MATIAS + LED
The 20R and 50R between LED and IC is only for thermal reduction, for mono red LED, if PV CC =V CC =3.3V, don't need these resistors
LED RING
VLP SELECT : 12mm from top of bottom board (pour matias cap afleurant top of top front layer) ROUND : 12 + 1.5 (rayon) - 2.7 (base datasheet) = 10.8mm ou plus (limité par matias cap bottom) Flat : 12 - 2.7 (base datasheet) = 9.3mm ou plus (limité par matias cap bottom)
